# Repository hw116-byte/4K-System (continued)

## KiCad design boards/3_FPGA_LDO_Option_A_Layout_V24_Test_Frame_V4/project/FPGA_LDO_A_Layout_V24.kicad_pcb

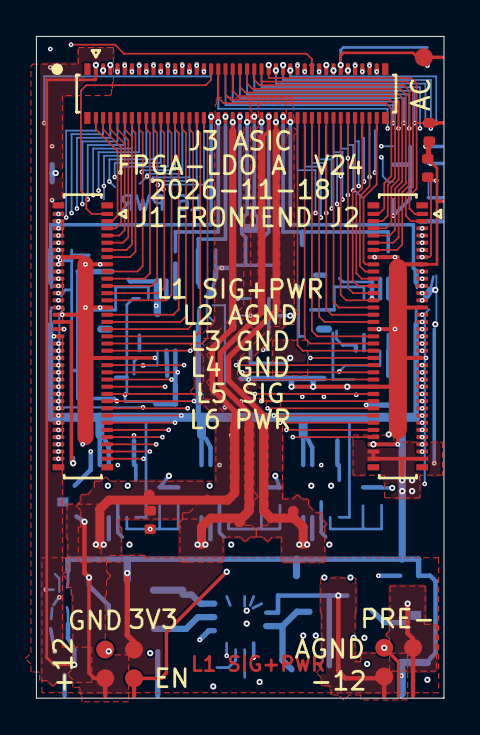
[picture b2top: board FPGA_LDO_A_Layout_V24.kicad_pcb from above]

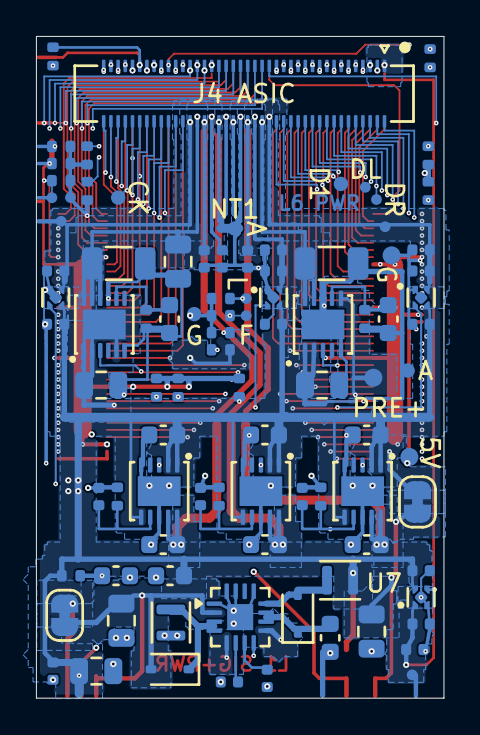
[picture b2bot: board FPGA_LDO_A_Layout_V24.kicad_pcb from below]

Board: 6 copper layers, 22.6 x 36.8 mm, 113 parts (96 on the bottom side), 150 nets.

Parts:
C1, C14, C21: 22uF; C_0805_2012Metric
C2: 100nF; C_0402_1005Metric
C3, C11: 4.7uF; C_0603_1608Metric
C15, C903, C1003: 1uF; C_0603_1608Metric
C16, C17: 10nF; C_0402_1005Metric
C51, C53, C54, C55, C56, C57, C203, C301, C302, C401, C402, C501, C502, C603, C701, C702, C803: 1uF; C_0402_1005Metric
C201, C202, C601, C602, C801, C802: 10uF; C_0603_1608Metric
C901, C1001, C1004: 10uF; C_0805_2012Metric
C902, C1002: 22uF; C_1206_3216Metric
D11, D12: B0540WS-TP; D_SOD-323
J1, J2: DF40C-70DP-0.4V(51); Hirose_DF40C-70DP-0.4V_2x35-1MP_P0.4mm
J3: DF40C-80DP-0.4V(51); Hirose_DF40C-80DP-0.4V_2x40-1MP_P0.4mm
J4: DF40C-80DS-0.4V(51); Hirose_DF40C-80DS-0.4V_2x40_P0.4mm
JP1, JP2: Bridged; SolderJumper-2_P1.3mm_Bridged_RoundedPad1.0x1.5mm
L11, L12: 6.8uH; L_Murata_DFE201610P
NT1: NetTie_2; NetTie-2_SMD_Pad0.5mm
R1, R2, R3, R4, R5, R6, R16, R17, R18, R19, R20, R21, R22, R23, R24, R25, R26, R27, R28: 10k; R_0402_1005Metric
R201, R601: 15k; R_0402_1005Metric
R801: 7.5k; R_0402_1005Metric
R802: 47k; R_0402_1005Metric
R901, R1001: 80.6k; R_0402_1005Metric
TP1: VIN_3V3; TestPoint_Pad_D1.0mm_Compact
TP2: STIM_POS_12V; TestPoint_Pad_D1.0mm_Compact
TP3: STIM_NEG_12V; TestPoint_Pad_D1.0mm_Compact
TP4: EN_ASIC_RAILS; TestPoint_Pad_D1.0mm_Compact
TP5: GND; TestPoint_Pad_D1.0mm_Compact
TP6: AGND; TestPoint_Pad_D1.0mm_Compact
TP7: ASIC_AC_IN; TestPoint_Pad_D1.0mm_Compact
TP8: STIM_PRE_POS; TestPoint_Pad_D1.0mm_Compact
TP9: STIM_PRE_NEG; TestPoint_Pad_D1.0mm_Compact
TP10: VIN_5V; TestPoint_Pad_D1.0mm_Compact
TP11: ASIC_VDD_FE; TestPoint_Pad_D0.6mm_Compact
TP12: ASIC_VDD_ADC; TestPoint_Pad_D0.6mm_Compact
TP14: ASIC_DVDD; TestPoint_Pad_D0.6mm_Compact
TP15: ASIC_REF_VDD; TestPoint_Pad_D0.6mm_Compact
TP16: ASIC_VDD_CGEN; TestPoint_Pad_D0.6mm_Compact
TP17: ASIC_REF_VCM; TestPoint_Pad_D0.6mm_Compact
TP20: ASIC4_SPI_DR; TestPoint_Pad_D0.6mm_Compact
TP21: ASIC4_SPI_DL; TestPoint_Pad_D0.6mm_Compact
TP22: ASIC4_DATA1; TestPoint_Pad_D0.8mm_Compact015
TP23: GND; TestPoint_Pad_D1.0mm_Compact015
TP24: ASIC3_4_TOP_SPI_CLK; TestPoint_Pad_D0.8mm_Compact015
TP25: STIM_START_SHARED; TestPoint_Pad_D0.6mm_Compact
TP26: GND; TestPoint_Pad_D0.6mm_Compact
TP27: BOARD1_SPI_LATCH; TestPoint_Pad_D0.6mm_Compact
TP28: FE_RESET_SHARED; TestPoint_Pad_D0.6mm_Compact
TP29: GND; TestPoint_Pad_D0.8mm_Compact015
TP30, TP31: AGND; TestPoint_Pad_D0.8mm_Compact015
U1: LT3582EUD-12#PBF; QFN-16-1EP_3x3mm_P0.5mm_EP1.45x1.45mm
U2, U6, U8, U9: LT3042EDD#PBF; DFN-10-1EP_3x3mm_P0.5mm_EP1.65x2.38mm
U3, U4, U5, U7: TPS7A2015PDQNR; Texas_X2SON-4_1x1mm_P0.65mm
U10: LT3094EDD#PBF; DFN-12-1EP_3x3mm_P0.45mm_EP1.65x2.38mm

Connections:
/ASIC1_CLK32MHz_Out: J2.59, J4.45
/ASIC1_DATA1: J2.21, J4.79
/ASIC1_DATA2: J2.64, J4.77
/ASIC1_DATA3: J2.62, J4.75
/ASIC1_DATA4: J2.60, J4.73
/ASIC1_DATA5: J2.57, J4.43
/ASIC1_DATA6: J2.55, J4.41
/ASIC1_DATA7: J2.53, J4.39
/ASIC1_DATA8: J2.51, J4.37
/ASIC1_READ: J2.49, J4.35
/ASIC1_SYNC: J2.61, J4.47
/ASIC2_CLK32MHz_Out: J1.63, J4.19
/ASIC2_DATA1: J1.70, J4.33
/ASIC2_DATA2: J1.51, J4.31
/ASIC2_DATA3: J1.53, J4.29
/ASIC2_DATA4: J1.55, J4.27
/ASIC2_DATA5: J1.65, J4.17
/ASIC2_DATA6: J1.67, J4.15
/ASIC2_DATA7: J1.69, J4.13
/ASIC2_DATA8: J1.38, J4.11
/ASIC2_READ: J1.40, J4.9
/ASIC2_SYNC: J1.61, J4.21
/ASIC3_4_TOP_SPI_CLK: J2.37, J4.72, R24.1, TP24.1
/ASIC3_4_TOP_SPI_LATCH: J2.35, J4.70, R26.1
/ASIC3_CLK32MHz_Out: J2.25, J4.62
/ASIC3_DATA1: J2.47, J4.80
/ASIC3_DATA2: J2.45, J4.78
/ASIC3_DATA3: J2.43, J4.76
/ASIC3_DATA4: J2.39, J4.74
/ASIC3_DATA5: J2.23, J4.60
/ASIC3_DATA6: J2.42, J4.58
/ASIC3_DATA7: J1.39, J4.32
/ASIC3_DATA8: J1.43, J4.30
/ASIC3_READ: J1.45, J4.28
/ASIC3_SPI_DL: J2.33, J4.68
/ASIC3_SPI_DR: J2.31, J4.66
/ASIC3_SYNC: J2.29, J4.64
/ASIC4_CLK32MHz_Out: J1.56, J4.12
/ASIC4_DATA1: J1.47, J4.26, TP22.1
/ASIC4_DATA2: J1.49, J4.24
/ASIC4_DATA3: J1.44, J4.22
/ASIC4_DATA4: J1.46, J4.20
/ASIC4_DATA5: J1.58, J4.10
/ASIC4_DATA6: J1.60, J4.8
/ASIC4_DATA7: J1.62, J4.6
/ASIC4_DATA8: J1.64, J4.4
/ASIC4_READ: J1.68, J4.2
/ASIC4_SPI_DL: J1.48, J4.18, TP21.1
/ASIC4_SPI_DR: J1.52, J4.16, TP20.1
/ASIC4_SYNC: J1.54, J4.14
/ASIC5_CLK32MHz_Out: J2.12, J3.45
/ASIC5_DATA1: J2.5, J3.79
/ASIC5_DATA2: J2.7, J3.77
/ASIC5_DATA3: J2.9, J3.75
/ASIC5_DATA4: J2.11, J3.73
/ASIC5_DATA5: J2.10, J3.43
/ASIC5_DATA6: J2.8, J3.41
/ASIC5_DATA7: J2.6, J3.39
/ASIC5_DATA8: J2.4, J3.37
/ASIC5_READ: J2.2, J3.35
/ASIC5_SYNC: J2.3, J3.47
/ASIC6_CLK32MHz_Out: J1.16, J3.19
/ASIC6_DATA1: J1.1, J3.33
/ASIC6_DATA2: J1.28, J3.31
/ASIC6_DATA3: J1.26, J3.29
/ASIC6_DATA4: J1.24, J3.27
/ASIC6_DATA5: J1.12, J3.17
/ASIC6_DATA6: J1.10, J3.15
/ASIC6_DATA7: J1.8, J3.13
/ASIC6_DATA8: J1.6, J3.11
/ASIC6_READ: J1.4, J3.9
/ASIC6_SYNC: J1.18, J3.21
/ASIC7_8_TOP_SPI_CLK: J2.24, J3.72, R25.1
/ASIC7_8_TOP_SPI_LATCH: J2.26, J3.70, R27.1
/ASIC7_CLK32MHz_Out: J2.36, J3.62
/ASIC7_DATA1: J2.16, J3.80
/ASIC7_DATA2: J2.18, J3.78
/ASIC7_DATA3: J2.20, J3.76
/ASIC7_DATA4: J2.22, J3.74
/ASIC7_DATA5: J2.38, J3.60
/ASIC7_DATA6: J2.40, J3.58
/ASIC7_DATA7: J1.37, J3.32
/ASIC7_DATA8: J1.35, J3.30
/ASIC7_READ: J1.33, J3.28
/ASIC7_SPI_DL: J2.28, J3.68
/ASIC7_SPI_DR: J2.30, J3.66
/ASIC7_SYNC: J2.32, J3.64
/ASIC8_CLK32MHz_Out: J1.13, J3.12
/ASIC8_DATA1: J1.31, J3.26
/ASIC8_DATA2: J1.29, J3.24
/ASIC8_DATA3: J1.25, J3.22
/ASIC8_DATA4: J1.23, J3.20
/ASIC8_DATA5: J1.11, J3.10
/ASIC8_DATA6: J1.9, J3.8
/ASIC8_DATA7: J1.7, J3.6
/ASIC8_DATA8: J1.5, J3.4
/ASIC8_READ: J1.3, J3.2
/ASIC8_SPI_DL: J1.21, J3.18
/ASIC8_SPI_DR: J1.19, J3.16
/ASIC8_SYNC: J1.17, J3.14
/ASIC_AC_IN: J3.69, J4.69, R6.1, TP7.1
/ASIC_DVDD: C54.1, C502.1, J3.34, J4.34, R19.2, TP14.1, U5.1
/ASIC_REF_VCM: C57.1, C802.1, J3.40, J4.40, R802.1, TP17.1, U8.9, U8.10
/ASIC_REF_VDD: C55.1, C602.1, J3.52, J4.52, TP15.1, U6.9, U6.10
/ASIC_VDD10: C902.1, J3.36, J4.36, U9.9, U9.10
/ASIC_VDD_ADC: C302.1, J3.56, J4.56, TP12.1, U3.1
/ASIC_VDD_CGEN: C56.1, C702.1, J3.1, J4.1, TP16.1, U7.1
/ASIC_VDD_DRIVER: C53.1, C402.1, J3.38, J4.38, U4.1
/ASIC_VDD_FE: C51.1, C202.1, J3.50, J4.50, TP11.1, U2.9, U2.10
/ASIC_VSS10: C1002.1, C1004.1, J3.54, J4.54, U10.10, U10.11, U10.12
/BOARD1_CLK: J1.42, J4.7, R20.1
/BOARD1_SPI_CLK: J2.52, J4.63, R22.1
/BOARD1_SPI_LATCH: J2.48, J4.61, R18.1, TP27.1
/BOARD3_CLK: J1.2, J3.7, R21.1
/BOARD3_SPI_CLK: J2.13, J3.63, R23.1
/BOARD3_SPI_LATCH: J1.36, J3.61, R28.1
/CAPP: C15.1, D11.1, U1.10, U1.11
/CHIP_RESET_SHARED: J2.58, J3.71, J4.71, R19.1
/EN_ASIC_RAILS: C3.1, R1.2, TP4.1, U1.8, U2.3, U3.3, U4.3, U5.3, U6.3, U7.3, U8.3, U9.3, U10.3
/FE_RESET_SHARED: J2.54, J3.65, J4.65, R16.1, TP28.1
/IMP_TST_SHARED: J2.56, J3.67, J4.67, R17.1
/RAMPN: C17.1, U1.6
/RAMPP: C16.1, U1.7
/STIM_CHB_SHARED: J2.1, J3.49, J4.49, R4.1
/STIM_CHIP1_SPI_DL: J2.46, J4.59
/STIM_CHIP1_SPI_DR: J2.44, J4.57
/STIM_CHIP2_SPI_DL: J1.57, J4.25
/STIM_CHIP2_SPI_DR: J1.59, J4.23
/STIM_CHIP3_SPI_DL: J2.17, J3.59
/STIM_CHIP3_SPI_DR: J2.19, J3.57
/STIM_CHIP4_SPI_DL: J1.22, J3.25
/STIM_CHIP4_SPI_DR: J1.20, J3.23
/STIM_CLK_SHARED: J2.65, J3.53, J4.53, R5.1
/STIM_EN_SHARED: J2.63, J3.51, J4.51, R2.1
/STIM_NEG_12V: C21.1, D12.2, JP2.1, TP3.1, U1.2
/STIM_POS_12V: C14.1, JP1.1, TP2.1, U1.9
/STIM_PRE_NEG: C1001.1, JP2.2, TP9.1, U10.1, U10.2, U10.5, U10.13
/STIM_PRE_POS: C901.1, JP1.2, TP8.1, U9.1, U9.2, U9.6
/STIM_START_SHARED: J2.67, J3.55, J4.55, R3.1, TP25.1
/SW_N: D12.1, L12.1, U1.3, U1.4
/SW_P: D11.2, L11.2, U1.12
/VIN_3V3: C1.1, C2.1, C11.1, C201.1, C301.1, C401.1, C501.1, C601.1, C701.1, C801.1, J2.68, J2.69, J2.70, L11.1, R1.1, TP1.1, U1.5, U2.1, U2.2, U2.6, U3.4, U4.4, U5.4, U6.1, U6.2, U6.6, U7.4, U8.1, U8.2, U8.6
/VIN_5V: J1.32, TP10.1
AGND: C51.2, C53.2, C55.2, C56.2, C57.2, C201.2, C202.2, C203.2, C301.2, C302.2, C401.2, C402.2, C601.2, C602.2, C603.2, C701.2, C702.2, C801.2, C802.2, C803.2, C901.2, C902.2, C903.2, C1001.2, C1002.2, C1003.2, C1004.2, J3.42, J3.44, J4.42, J4.44, NT1.2, R6.2, R201.2, R601.2, R801.2, R802.2, R901.2, R1001.2, TP6.1, TP30.1, TP31.1, U2.5, U2.8, U2.11, U3.2, U3.5, U4.2, U4.5, U6.5, U6.8, U6.11, U7.2, U7.5, U8.5, U8.8, U8.11, U9.5, U9.8, U9.11, U10.6, U10.9
GND: C1.2, C2.2, C3.2, C11.2, C14.2, C15.2, C16.2, C17.2, C21.2, C54.2, C501.2, C502.2, J1.14, J1.15, J1.27, J1.30, J1.34, J1.41, J1.50, J1.66, J2.14, J2.15, J2.27, J2.34, J2.41, J2.50, J2.66, J3.3, J3.5, J3.46, J3.48, J4.3, J4.5, J4.46, J4.48, L12.2, NT1.1, R2.2, R3.2, R4.2, R5.2, R16.2, R17.2, R18.2, R20.2, R21.2, R22.2, R23.2, R24.2, R25.2, R26.2, R27.2, R28.2, TP5.1, TP23.1, TP26.1, TP29.1, U1.1, U1.13, U1.15, U1.16, U1.17, U5.2, U5.5
unnamed: C203.1, R201.1, U2.7
unnamed: C603.1, R601.1, U6.7
unnamed: C803.1, R801.1, U8.7
unnamed: C903.1, R901.1, U9.7
unnamed: C1003.1, R1001.1, U10.8

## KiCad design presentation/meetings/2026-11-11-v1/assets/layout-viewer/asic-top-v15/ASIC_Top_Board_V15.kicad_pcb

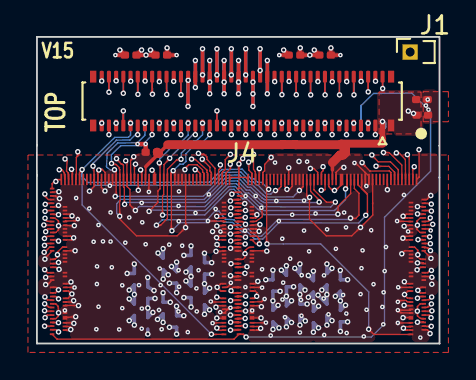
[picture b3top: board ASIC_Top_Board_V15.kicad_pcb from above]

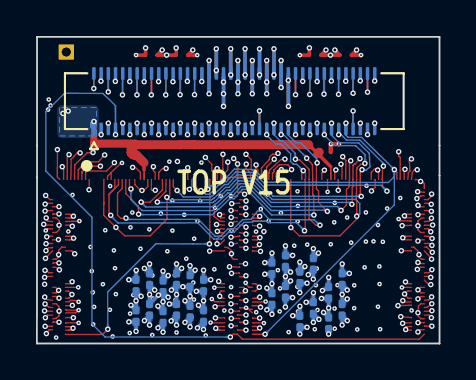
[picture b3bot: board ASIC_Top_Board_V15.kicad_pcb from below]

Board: 10 copper layers, 22.4 x 17.0 mm, 36 parts (25 on the bottom side), 76 nets.

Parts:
C1, C2, C4, C5, C6, C7, C14, C18, C25, C33, C34, C41, C42, C46, C48: 10nF; C_0201_0603Metric
C19, C26, C50, C51, C52, C53, C54, C55, C56, C57, C58, C59, C60, C61, C62, C63: 100nF; C_0201_0603Metric
J1: Conn_01x01_Pin; PinHeader_1x01_P1.00mm_Horizontal
J3: DF40C-80DS-0.4V(51); Hirose_DF40C-80DS-0.4V_2x40_P0.4mm
J4: DF40C-80DP-0.4V(51); Hirose_DF40C-80DP-0.4V_2x40-1MP_P0.4mm
U01_BCD1, U01_BCD2: *; U01_BCD_OFF_CHIP

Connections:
/AC_IN: J3.69, J4.69, U01_BCD1.AC_IN, U01_BCD2.AC_IN
/AGND: C1.2, C2.2, C4.2, C5.2, C6.2, C18.2, C19.2, C25.2, C26.2, C33.2, C34.2, C41.2, C42.2, C46.2, C48.2, C50.2, C51.2, C52.2, C53.2, C54.2, C55.2, C56.2, C57.2, C58.2, C59.2, C60.2, C63.2, J1.1 (Pin_1_1), J3.42, J3.44, J4.42, J4.44, U01_BCD1.AGND2, U01_BCD1.AGND_1, U01_BCD1.LAGND_1, U01_BCD1.LAGND_2, U01_BCD1.LAGND_3, U01_BCD1.LAGND_4, U01_BCD1.LAGND_5, U01_BCD1.LAGND_6, U01_BCD1.LAGND_7, U01_BCD1.LAGND_8, U01_BCD1.LAGND_9, U01_BCD1.LAGND_10, U01_BCD1.LAGND_11, U01_BCD1.LAGND_12, U01_BCD1.LAGND_13, U01_BCD1.LAGND_14, U01_BCD1.LAGND_15, U01_BCD1.LREF_GND1, U01_BCD1.LREF_GND2, U01_BCD1.LREF_GND3, U01_BCD1.LREF_GND4, U01_BCD1.RAGND_1, U01_BCD1.RAGND_2, U01_BCD1.RAGND_3, U01_BCD1.RAGND_4, U01_BCD1.RAGND_5, U01_BCD1.RAGND_6, U01_BCD1.RAGND_7, U01_BCD1.RAGND_8, U01_BCD1.RAGND_9, U01_BCD1.RAGND_10, U01_BCD1.RAGND_11, U01_BCD1.RAGND_12, U01_BCD1.RAGND_13, U01_BCD1.RAGND_14, U01_BCD1.RAGND_15, U01_BCD1.REF_1, U01_BCD1.REF_2, U01_BCD1.REF_3, U01_BCD1.REF_4, U01_BCD1.RREF_GND1, U01_BCD1.RREF_GND2, U01_BCD1.RREF_GND3, U01_BCD1.RREF_GND4, U01_BCD2.AGND2, U01_BCD2.AGND_1, U01_BCD2.LAGND_1, U01_BCD2.LAGND_2, U01_BCD2.LAGND_3, U01_BCD2.LAGND_4, U01_BCD2.LAGND_5, U01_BCD2.LAGND_6, U01_BCD2.LAGND_7, U01_BCD2.LAGND_8, U01_BCD2.LAGND_9, U01_BCD2.LAGND_10, U01_BCD2.LAGND_11, U01_BCD2.LAGND_12, U01_BCD2.LAGND_13, U01_BCD2.LAGND_14, U01_BCD2.LAGND_15, U01_BCD2.LREF_GND1, U01_BCD2.LREF_GND2, U01_BCD2.LREF_GND3, U01_BCD2.LREF_GND4, U01_BCD2.RAGND_1, U01_BCD2.RAGND_2, U01_BCD2.RAGND_3, U01_BCD2.RAGND_4, U01_BCD2.RAGND_5, U01_BCD2.RAGND_6, U01_BCD2.RAGND_7, U01_BCD2.RAGND_8, U01_BCD2.RAGND_9, U01_BCD2.RAGND_10, U01_BCD2.RAGND_11, U01_BCD2.RAGND_12, U01_BCD2.RAGND_13, U01_BCD2.RAGND_14, U01_BCD2.RAGND_15, U01_BCD2.REF_1, U01_BCD2.REF_2, U01_BCD2.REF_3, U01_BCD2.REF_4, U01_BCD2.RREF_GND1, U01_BCD2.RREF_GND2, U01_BCD2.RREF_GND3, U01_BCD2.RREF_GND4
/CHIP_RESET: J3.71, J4.71, U01_BCD1.RRST_DIGITAL, U01_BCD1.RST_DRIVER, U01_BCD2.RRST_DIGITAL, U01_BCD2.RST_DRIVER
/CLK32MHZ: J3.45, J4.45
/CLK32MHZ(2): J3.19, J4.19
/CLKH: J3.7, J4.7, U01_BCD1.CLKH, U01_BCD2.CLKH
/D<1>: J3.79, J4.79
/D<1>(2): J3.33, J4.33
/D<2>: J3.77, J4.77
/D<2>(2): J3.31, J4.31
/D<3>: J3.75, J4.75
/D<3>(2): J3.29, J4.29
/D<4>: J3.73, J4.73
/D<4>(2): J3.27, J4.27
/D<5>: J3.43, J4.43
/D<5>(2): J3.17, J4.17
/D<6>: J3.41, J4.41
/D<6>(2): J3.15, J4.15
/D<7>: J3.39, J4.39
/D<7>(2): J3.13, J4.13
/D<8>: J3.37, J4.37
/D<8>(2): J3.11, J4.11
/DGND: C7.2, C14.2, C61.2, C62.2, J3.3, J3.5, J3.46, J3.48, J4.3, J4.5, J4.46, J4.48, U01_BCD1.DGND1, U01_BCD1.DGND2, U01_BCD1.DGND3, U01_BCD1.DGND4, U01_BCD1.EN_LDO, U01_BCD1.LDGND_1, U01_BCD1.LDGND_2, U01_BCD1.LDGND_3, U01_BCD1.LDGND_4, U01_BCD1.LDGND_5, U01_BCD1.LDGND_6, U01_BCD1.LDGND_7, U01_BCD1.LDGND_8, U01_BCD1.LDGND_9, U01_BCD1.LDGND_10, U01_BCD1.LDGND_11, U01_BCD1.LDGND_12, U01_BCD1.LDGND_13, U01_BCD1.RDGND_1, U01_BCD1.RDGND_2, U01_BCD1.RDGND_3, U01_BCD1.RDGND_4, U01_BCD1.RDGND_5, U01_BCD1.RDGND_6, U01_BCD1.RDGND_7, U01_BCD1.RDGND_8, U01_BCD1.RDGND_9, U01_BCD1.RDGND_10, U01_BCD1.RDGND_11, U01_BCD1.RDGND_12, U01_BCD1.RDGND_13, U01_BCD2.DGND1, U01_BCD2.DGND2, U01_BCD2.DGND3, U01_BCD2.DGND4, U01_BCD2.EN_LDO, U01_BCD2.LDGND_1, U01_BCD2.LDGND_2, U01_BCD2.LDGND_3, U01_BCD2.LDGND_4, U01_BCD2.LDGND_5, U01_BCD2.LDGND_6, U01_BCD2.LDGND_7, U01_BCD2.LDGND_8, U01_BCD2.LDGND_9, U01_BCD2.LDGND_10, U01_BCD2.LDGND_11, U01_BCD2.LDGND_12, U01_BCD2.LDGND_13, U01_BCD2.RDGND_1, U01_BCD2.RDGND_2, U01_BCD2.RDGND_3, U01_BCD2.RDGND_4, U01_BCD2.RDGND_5, U01_BCD2.RDGND_6, U01_BCD2.RDGND_7, U01_BCD2.RDGND_8, U01_BCD2.RDGND_9, U01_BCD2.RDGND_10, U01_BCD2.RDGND_11, U01_BCD2.RDGND_12, U01_BCD2.RDGND_13
/DVDD: C7.1, C14.1, C61.1, C62.1, J3.34, J4.34, U01_BCD1.CGEN_RST, U01_BCD1.LDVDD_B1, U01_BCD1.LDVDD_B2, U01_BCD1.LDVDD_B3, U01_BCD1.LDVDD_T1, U01_BCD1.LDVDD_T2, U01_BCD1.LDVDD_T3, U01_BCD1.RDVDD_B1, U01_BCD1.RDVDD_B2, U01_BCD1.RDVDD_B3, U01_BCD1.RDVDD_T1, U01_BCD1.RDVDD_T2, U01_BCD1.RDVDD_T3, U01_BCD1.SPI_LDO_O, U01_BCD1.SPI_LDO_P, U01_BCD1.SPI_LDO_P1, U01_BCD1.SPI_LDO_P2, U01_BCD2.CGEN_RST, U01_BCD2.LDVDD_B1, U01_BCD2.LDVDD_B2, U01_BCD2.LDVDD_B3, U01_BCD2.LDVDD_T1, U01_BCD2.LDVDD_T2, U01_BCD2.LDVDD_T3, U01_BCD2.RDVDD_B1, U01_BCD2.RDVDD_B2, U01_BCD2.RDVDD_B3, U01_BCD2.RDVDD_T1, U01_BCD2.RDVDD_T2, U01_BCD2.RDVDD_T3, U01_BCD2.SPI_LDO_O, U01_BCD2.SPI_LDO_P, U01_BCD2.SPI_LDO_P1, U01_BCD2.SPI_LDO_P2
/FE_RESET: J3.65, J4.65, U01_BCD1.RST_FEL, U01_BCD1.RST_FER, U01_BCD2.RST_FEL, U01_BCD2.RST_FER
/IMP_TEST: J3.67, J4.67, U01_BCD1.IMP_TST, U01_BCD2.IMP_TST
/READ: J3.35, J4.35
/READ(2): J3.9, J4.9
/REF_VCM: C5.1, C46.1, C57.1, C58.1, J3.40, J4.40, U01_BCD1.LREF_VCM1, U01_BCD1.LREF_VCM2, U01_BCD1.LREF_VCM3, U01_BCD1.LREF_VCM4, U01_BCD1.RREF_VCM1, U01_BCD1.RREF_VCM2, U01_BCD1.RREF_VCM3, U01_BCD1.RREF_VCM4, U01_BCD1.VCM, U01_BCD2.LREF_VCM1, U01_BCD2.LREF_VCM2, U01_BCD2.LREF_VCM3, U01_BCD2.LREF_VCM4, U01_BCD2.RREF_VCM1, U01_BCD2.RREF_VCM2, U01_BCD2.RREF_VCM3, U01_BCD2.RREF_VCM4, U01_BCD2.VCM
/REF_VDD: C2.1, C33.1, C55.1, C56.1, J3.52, J4.52, U01_BCD1.LREF_VDD1, U01_BCD1.LREF_VDD2, U01_BCD1.LREF_VDD3, U01_BCD1.LREF_VDD4, U01_BCD1.RREF_VDD1, U01_BCD1.RREF_VDD2, U01_BCD1.RREF_VDD3, U01_BCD1.RREF_VDD4, U01_BCD2.LREF_VDD1, U01_BCD2.LREF_VDD2, U01_BCD2.LREF_VDD3, U01_BCD2.LREF_VDD4, U01_BCD2.RREF_VDD1, U01_BCD2.RREF_VDD2, U01_BCD2.RREF_VDD3, U01_BCD2.RREF_VDD4
/SPI_CLK: J3.63, J4.63
/SPI_DINL: J3.59, J4.59
/SPI_DINL(2): J3.25, J4.25
/SPI_DINR: J3.57, J4.57
/SPI_DINR(2): J3.23, J4.23
/SPI_LATCH: J3.61, J4.61
/STIM_CHB: J3.49, J4.49, U01_BCD1.FPGA_CHBL, U01_BCD1.FPGA_CHBR, U01_BCD2.FPGA_CHBL, U01_BCD2.FPGA_CHBR
/STIM_CLK: J3.53, J4.53, U01_BCD1.FPGA_CLK, U01_BCD2.FPGA_CLK
/STIM_EN: J3.51, J4.51, U01_BCD1.FPGA_EN, U01_BCD2.FPGA_EN
/STIM_START: J3.55, J4.55, U01_BCD1.FPGA_START, U01_BCD2.FPGA_START
/SYNC: J3.47, J4.47
/SYNC(2): J3.21, J4.21
/T_CLK32MHZ: J3.62, J4.62, U01_BCD1.CLK32MHZ
/T_CLK32MHZ(2): J3.12, J4.12, U01_BCD2.CLK32MHZ
/T_D<1>: J3.80, J4.80, U01_BCD1.DATAL<4>
/T_D<1>(2): J3.26, J4.26, U01_BCD2.DATAL<4>
/T_D<2>: J3.78, J4.78, U01_BCD1.DATAL<3>
/T_D<2>(2): J3.24, J4.24, U01_BCD2.DATAL<3>
/T_D<3>: J3.76, J4.76, U01_BCD1.DATAL<2>
/T_D<3>(2): J3.22, J4.22, U01_BCD2.DATAL<2>
/T_D<4>: J3.74, J4.74, U01_BCD1.DATAL<1>
/T_D<4>(2): J3.20, J4.20, U01_BCD2.DATAL<1>
/T_D<5>: J3.60, J4.60, U01_BCD1.DATAR<4>
/T_D<5>(2): J3.10, J4.10, U01_BCD2.DATAR<4>
/T_D<6>: J3.58, J4.58, U01_BCD1.DATAR<3>
/T_D<6>(2): J3.8, J4.8, U01_BCD2.DATAR<3>
/T_D<7>: J3.32, J4.32, U01_BCD1.DATAR<2>
/T_D<7>(2): J3.6, J4.6, U01_BCD2.DATAR<2>
/T_D<8>: J3.30, J4.30, U01_BCD1.DATAR<1>
/T_D<8>(2): J3.4, J4.4, U01_BCD2.DATAR<1>
/T_READ: J3.28, J4.28, U01_BCD1.READ
/T_READ(2): J3.2, J4.2, U01_BCD2.READ
/T_SPI_CLK: J3.72, J4.72, U01_BCD1.SPI_CLK, U01_BCD2.SPI_CLK
/T_SPI_DINL: J3.68, J4.68, U01_BCD1.SPI_DINL
/T_SPI_DINL(2): J3.18, J4.18, U01_BCD2.SPI_DINL
/T_SPI_DINR: J3.66, J4.66, U01_BCD1.SPI_DINR
/T_SPI_DINR(2): J3.16, J4.16, U01_BCD2.SPI_DINR
/T_SPI_LATCH: J3.70, J4.70, U01_BCD1.SPI_LATCH, U01_BCD2.SPI_LATCH
/T_SYNC: J3.64, J4.64, U01_BCD1.SYNC
/T_SYNC(2): J3.14, J4.14, U01_BCD2.SYNC
/VDD10: C18.1, C19.1, J3.36, J4.36, U01_BCD1.P10_L, U01_BCD1.P10_R, U01_BCD2.P10_L, U01_BCD2.P10_R
/VDD_ADC: C1.1, C34.1, C53.1, C54.1, J3.56, J4.56, U01_BCD1.LVDD_ADC1, U01_BCD1.LVDD_ADC2, U01_BCD1.LVDD_ADC3, U01_BCD1.LVDD_ADC4, U01_BCD1.LVDD_ADC5, U01_BCD1.RVDD_ADC1, U01_BCD1.RVDD_ADC2, U01_BCD1.RVDD_ADC3, U01_BCD1.RVDD_ADC4, U01_BCD1.RVDD_ADC5, U01_BCD2.LVDD_ADC1, U01_BCD2.LVDD_ADC2, U01_BCD2.LVDD_ADC3, U01_BCD2.LVDD_ADC4, U01_BCD2.LVDD_ADC5, U01_BCD2.RVDD_ADC1, U01_BCD2.RVDD_ADC2, U01_BCD2.RVDD_ADC3, U01_BCD2.RVDD_ADC4, U01_BCD2.RVDD_ADC5
/VDD_CGEN: C6.1, C50.1, C63.1, J3.1, J4.1, U01_BCD1.VDD_CGEN, U01_BCD2.VDD_CGEN
/VDD_DRIVER: C41.1, C42.1, C59.1, C60.1, J3.38, J4.38, U01_BCD1.LVDD_DRIVER1, U01_BCD1.LVDD_DRIVER2, U01_BCD1.LVDD_DRIVER3, U01_BCD1.LVDD_DRIVER4, U01_BCD1.LVDD_DRIVER5, U01_BCD1.RVDD_DRIVER1, U01_BCD1.RVDD_DRIVER2, U01_BCD1.RVDD_DRIVER3, U01_BCD1.RVDD_DRIVER4, U01_BCD1.RVDD_DRIVER5, U01_BCD2.LVDD_DRIVER1, U01_BCD2.LVDD_DRIVER2, U01_BCD2.LVDD_DRIVER3, U01_BCD2.LVDD_DRIVER4, U01_BCD2.LVDD_DRIVER5, U01_BCD2.RVDD_DRIVER1, U01_BCD2.RVDD_DRIVER2, U01_BCD2.RVDD_DRIVER3, U01_BCD2.RVDD_DRIVER4, U01_BCD2.RVDD_DRIVER5
/VDD_FE: C4.1, C48.1, C51.1, C52.1, J3.50, J4.50, U01_BCD1.LVDD_FE1, U01_BCD1.LVDD_FE2, U01_BCD1.LVDD_FE3, U01_BCD1.LVDD_FE4, U01_BCD1.RVDD_FE1, U01_BCD1.RVDD_FE2, U01_BCD1.RVDD_FE3, U01_BCD1.RVDD_FE4, U01_BCD2.LVDD_FE1, U01_BCD2.LVDD_FE2, U01_BCD2.LVDD_FE3, U01_BCD2.LVDD_FE4, U01_BCD2.RVDD_FE1, U01_BCD2.RVDD_FE2, U01_BCD2.RVDD_FE3, U01_BCD2.RVDD_FE4
/VSS10: C25.1, C26.1, J3.54, J4.54, U01_BCD1.M10_L, U01_BCD1.M10_R, U01_BCD2.M10_L, U01_BCD2.M10_R

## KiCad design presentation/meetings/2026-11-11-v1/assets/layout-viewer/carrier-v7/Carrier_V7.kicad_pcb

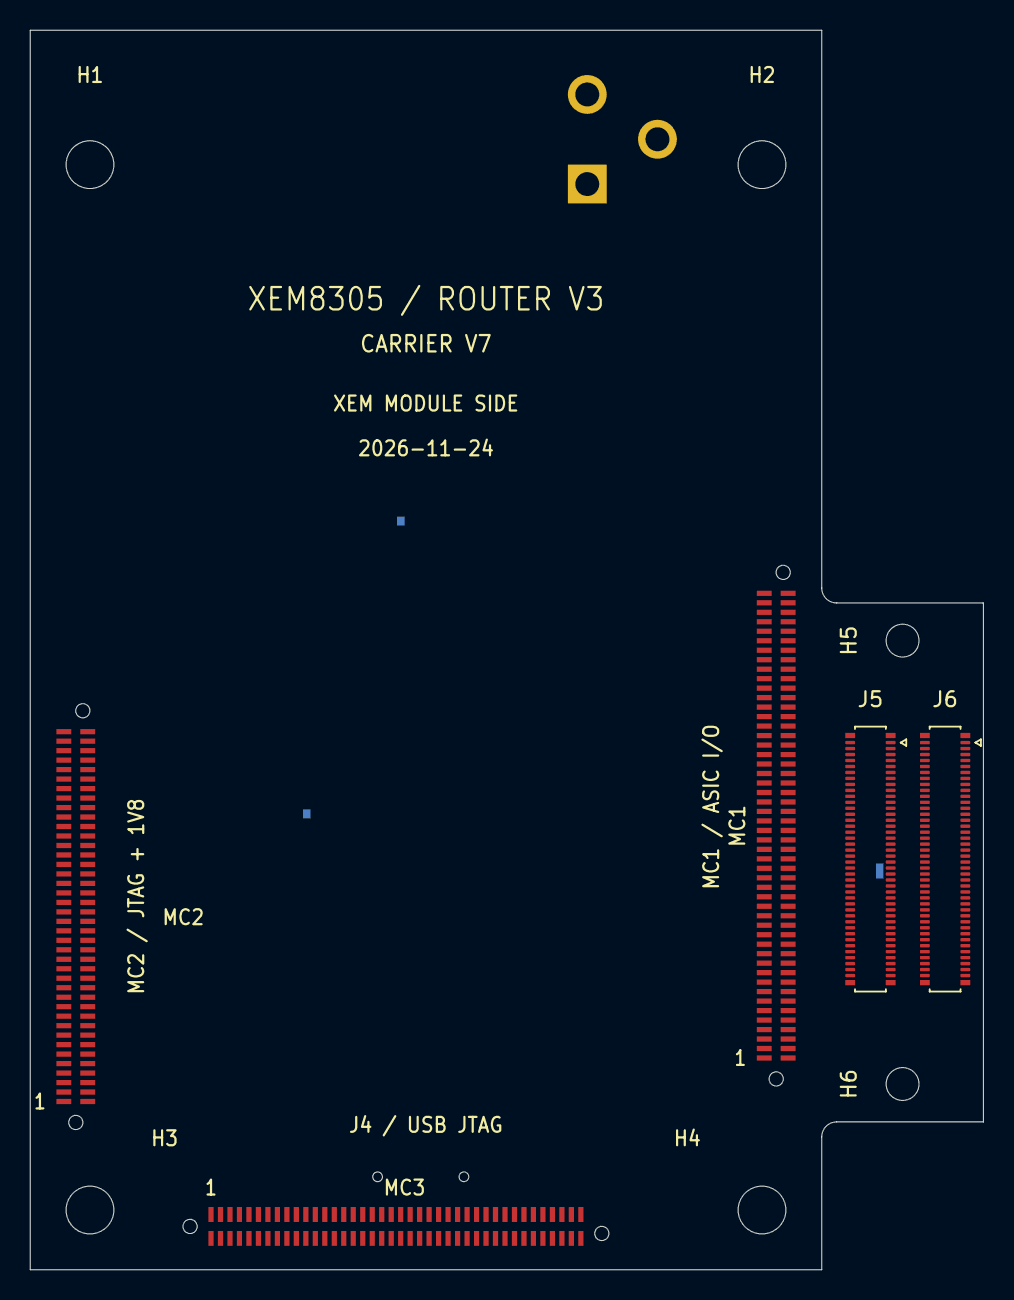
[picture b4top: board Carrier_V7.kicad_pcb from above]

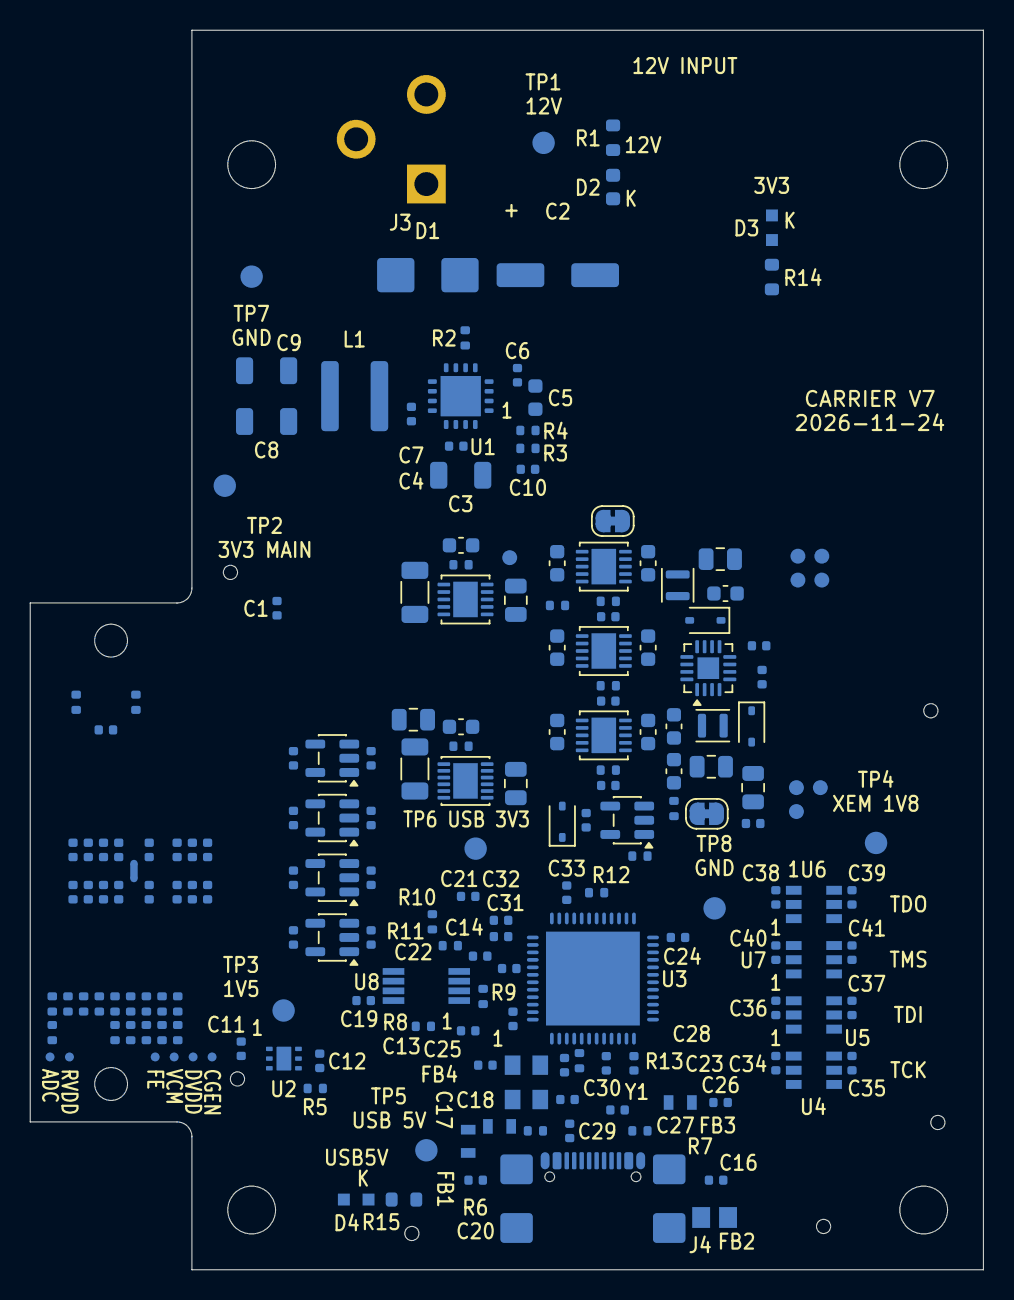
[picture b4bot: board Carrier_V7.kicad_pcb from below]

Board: 6 copper layers, 63.8 x 83.0 mm, 203 parts (192 on the bottom side), 193 nets, no tracks yet.

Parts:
C1: 0.1u 25v; C_0402_1005Metric
C2: 220u 25v; CP_Panasonic_EEEFTE221XAL_D6.3x7.7_V3
C3: 22u 35V; C_1206_3216Metric
C4: 0.1u 25V; C_0402_1005Metric
C5: 1u 25V; C_0603_1608Metric
C6: 3.3n 50V; C_0402_1005Metric
C7: 0.1u 16V; C_0402_1005Metric
C8, C9: 22u 10V; C_1206_3216Metric
C10: 10p 50V; C_0402_1005Metric
C11, C12: 4.7u 10V X5R; C_0402_1005Metric
C13, C21, C26, C27, C29: 4.7u; C_0402_1005Metric
C14, C16, C19, C22, C23, C24, C25, C28, C30, C31, C32, C34, C35, C36, C37, C38, C39, C40, C41: 100n; C_0402_1005Metric
C15, C903, C1003: 1uF; C_0603_1608Metric
C17, C18: 18p; C_0402_1005Metric
C20, C33: 10n; C_0402_1005Metric
C42, C46, C49: 22uF; C_0805_2012Metric
C43, C68: 100nF; C_0402_1005Metric
C44, C45: 4.7uF; C_0603_1608Metric
C47, C48: 10nF; C_0402_1005Metric
C51, C52, C53, C54, C55, C56, C57, C58, C59, C60, C61, C62, C63, C64, C65, C66, C67, C203, C301, C302, C401, C402, C501, C502, C603, C701, C702, C803: 1uF; C_0402_1005Metric
C201, C202, C601, C602, C801, C802: 10uF; C_0603_1608Metric
C901, C1001, C1004: 10uF; C_0805_2012Metric
C902, C1002: 22uF; C_1206_3216Metric
D1: SMBJ15CA-13-F; D_SMB
D2: 598-8070-107F; LED_0603_1608Metric
D3: APT1608LZGCK; LED_Kingbright_APT1608LZGCK_V2
D4: APT1608LSYCK/J3-PRV; LED_Kingbright_APT1608LSYCK_J3_PRV_V2
D11, D12, D13: B0540WS-TP; D_SOD-323
FB1, FB3, FB4: 600R; Ferrite_Bead_Murata_BLM18KG601SN1D_0603_V4
FB2: 220R @100MHz; BRK8305_A03_FB503
H1, H2, H3, H4: XEM M3 NPTH; MountingHole_3.2mm_XEM_M3_Keepout
H5, H6: M2 holder NPTH; MountingHole_2.2mm_M2
J3: PJ-102AH; PJ102AH
J4: USB4110-GF-A; USB_C_Receptacle_GCT_USB4110_GF_A_Horizontal
J5, J6: DF40C-80DP-0.4V(51); Hirose_DF40C-80DP-0.4V_2x40-1MP_P0.4mm
JP1, JP2: Bridged; SolderJumper-2_P1.3mm_Bridged_RoundedPad1.0x1.5mm
L1: 2.2uH; L_Coilcraft_XAL5030-332MEC
L11, L12: 6.8uH; L_Murata_DFE201610P
MC1: ERF6-50-03.5-L-DV-A-K-TR
MC2: XEM_MC2_80; ERF6-40-03.5-L-DV-A-K-TR
MC3: XEM_MC3_80; ERF6-40-03.5-L-DV-A-K-TR
NT1: NetTie_2; NetTie-2_SMD_Pad0.5mm
R1: 2.0k; R_0603_1608Metric
R2: 10k 1%; R_0402_1005Metric
R3: 73.2k 1%; R_0402_1005Metric
R4: 22.1k 1%; R_0402_1005Metric
R5, R8, R9: 100k; R_0402_1005Metric
R6, R7: 5.1k 1%; R_0402_1005Metric
R10: 2k; R_0402_1005Metric
R11, R12, R16, R17, R18, R19, R20, R21, R22, R23, R24, R25, R26, R27, R28, R29, R30, R31, R32, R33: 10k; R_0402_1005Metric
R13: 12k 1%; R_0402_1005Metric
R14: 3.0k 1%; R_0603_1608Metric
R15: 6.8k 1%; R_0603_1608Metric
R34: 220; R_0402_1005Metric
R201, R601: 15k; R_0402_1005Metric
R801: 7.5k; R_0402_1005Metric
R802: 47k; R_0402_1005Metric
R901, R1001: 80.6k; R_0402_1005Metric
TP1: 12V; TestPoint_Pad_D1.5mm
TP2: 3V3_MAIN; TestPoint_Pad_D1.5mm
TP3: 1V5; TestPoint_Pad_D1.5mm
TP4: XEM_1V8; TestPoint_Pad_D1.5mm
TP5: USB_5V; TestPoint_Pad_D1.5mm
TP6: USB_3V3; TestPoint_Pad_D1.5mm
TP7: GND_PWR; TestPoint_Pad_D1.5mm
TP8: GND_USB; TestPoint_Pad_D1.5mm
TP11: ASIC_VDD_FE; TestPoint_Pad_D0.6mm_Compact
TP12: ASIC_VDD_ADC; TestPoint_Pad_D0.6mm_Compact
TP14: ASIC_DVDD; TestPoint_Pad_D0.6mm_Compact
TP15: ASIC_REF_VDD; TestPoint_Pad_D0.6mm_Compact
TP16: ASIC_VDD_CGEN; TestPoint_Pad_D0.6mm_Compact
TP17: ASIC_REF_VCM; TestPoint_Pad_D0.6mm_Compact
TP31: +3V3; TestPoint_Pad_D1.0mm_Compact
TP32: STIM_POS_12V; TestPoint_Pad_D1.0mm_Compact
TP33: STIM_NEG_12V; TestPoint_Pad_D1.0mm_Compact
TP34: EN_ASIC_RAILS; TestPoint_Pad_D1.0mm_Compact
TP35: GND; TestPoint_Pad_D1.0mm_Compact
TP36: AGND; TestPoint_Pad_D1.0mm_Compact
TP38: STIM_PRE_POS; TestPoint_Pad_D1.0mm_Compact
TP39: STIM_PRE_NEG; TestPoint_Pad_D1.0mm_Compact
U1: TPS54429ERSAT; TPS54429E_RSA
U2: TLV75515PDRVR; Texas_WSON-6_2x2mm_P0.65mm_EP1x1.6mm_TLV755_DRV_V2
U3: FT232HQ; BRK8305_A03_U501
U4, U5, U6, U7: SN74AXC1T45DBVR; BRK8305_A03_U500
U8: 93AA56B-I/MS; BRK8305_A03_U505
U11: LT3582EUD-12#PBF; QFN-16-1EP_3x3mm_P0.5mm_EP1.45x1.45mm
U12, U16, U18, U19: LT3042EDD#PBF; DFN-10-1EP_3x3mm_P0.5mm_EP1.65x2.38mm
U13, U14, U15, U17: TPS7A2015PDBVR; SOT-23-5
U20: LT3094EDD#PBF; DFN-12-1EP_3x3mm_P0.45mm_EP1.65x2.38mm
U21: SN74LV1T34DBVR; SOT-23-5
Y1: 12MHz; BRK8305_A03_Y500

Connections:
+1V5: C11.1, MC1.1, MC1.2, MC1.3, MC1.4, MC2.37, MC2.39, MC2.41, MC2.43, TP3.1, U2.1
+3V3: C8.1, C9.1, C10.1, C12.1, C42.1, C43.1, C45.1, C68.1, C201.1, C301.1, C401.1, C501.1, C601.1, C701.1, C801.1, L1.2, L11.1, R3.1, R14.1, TP2.1, TP31.1, U1.16, U2.6, U11.5, U12.1, U12.2, U12.6, U13.1, U14.1, U15.1, U16.1, U16.2, U16.6, U17.1, U18.1, U18.2, U18.6, U21.5
+12V: C1.1, C2.1, C3.1, C4.1, D1.2, J3.1, MC1.91, MC1.93, MC1.95, MC1.97, MC1.99, R1.1, R2.1, TP1.1, U1.13, U1.14, U1.15
/ASIC_Rails/ASIC_EN_SRC: D13.1, R29.1, U21.4
/ASIC_Rails/CAPP: C15.1, D11.1, U11.10, U11.11
/ASIC_Rails/EN_ASIC_RAILS: C44.1, R29.2, R34.2, TP34.1, U11.8, U12.3, U13.3, U14.3, U15.3, U16.3, U17.3, U18.3, U19.3, U20.3
/ASIC_Rails/RAMPN: C48.1, U11.6
/ASIC_Rails/RAMPP: C47.1, U11.7
/ASIC_Rails/STIM_NEG_12V: C49.1, D12.2, JP2.1, TP33.1, U11.2
/ASIC_Rails/STIM_POS_12V: C46.1, JP1.1, TP32.1, U11.9
/ASIC_Rails/STIM_PRE_NEG: C1001.1, JP2.2, TP39.1, U20.1, U20.2, U20.5, U20.13
/ASIC_Rails/STIM_PRE_POS: C901.1, JP1.2, TP38.1, U19.1, U19.2, U19.6
/ASIC_Rails/SW_N: D12.1, L12.1, U11.3, U11.4
/ASIC_Rails/SW_P: D11.2, L11.2, U11.12
/Router_Interface/ASIC_AC_IN: J5.69, J6.70
/XEM_Power_USB/FB_BUCK: C10.2, R3.2, R4.1, U1.1
/XEM_Power_USB/USBJTAG_1.8V_ANALOG: C32.2, U3.37
/XEM_Power_USB/USBJTAG_1.8V_CORE: C31.2, U3.38
/XEM_Power_USB/USBJTAG_3.3V: C19.1, C21.1, C22.1, C23.1, C24.1, C25.1, C26.1, C34.1, C36.1, C38.1, C40.1, FB3.1, FB4.1, R9.1, R11.2, R12.1, TP6.1, U3.12, U3.24, U3.39, U3.46, U4.1, U4.5, U5.1, U5.5, U6.1, U7.1, U7.5, U8.8
/XEM_Power_USB/USBJTAG_3.3V_PHY: C29.1, C30.1, FB4.2, U3.3
/XEM_Power_USB/USBJTAG_3.3V_PLL: C27.1, C28.1, FB3.2, U3.8
/XEM_Power_USB/USBJTAG_5V_FILTERED: C13.1, C14.1, FB1.2, U3.40
/XEM_Power_USB/USBJTAG_EECLK: R9.2, U3.44, U8.2
/XEM_Power_USB/USBJTAG_EECS: R8.1, U3.45, U8.1
/XEM_Power_USB/USBJTAG_EEDATA: R10.1, U3.43, U8.3
/XEM_Power_USB/XEM_1.8V: C35.1, C37.1, C39.1, C41.1, MC2.75, MC2.77, MC2.79, TP4.1, U4.6, U5.6, U6.6, U7.6
AGND: C51.2, C52.2, C53.2, C55.2, C56.2, C57.2, C58.2, C59.2, C61.2, C62.2, C63.2, C64.2, C65.2, C66.2, C67.2, C201.2, C202.2, C203.2, C301.2, C302.2, C401.2, C402.2, C601.2, C602.2, C603.2, C701.2, C702.2, C801.2, C802.2, C803.2, C901.2, C902.2, C903.2, C1001.2, C1002.2, C1003.2, C1004.2, J5.42, J5.44, J6.41, J6.43, NT1.2, R201.2, R601.2, R801.2, R802.2, R901.2, R1001.2, TP36.1, U12.5, U12.8, U12.11, U13.2, U14.2, U16.5, U16.8, U16.11, U17.2, U18.5, U18.8, U18.11, U19.5, U19.8, U19.11, U20.6, U20.9
ASIC1_CLK32MHz_Out: J6.46, MC1.52
ASIC1_DATA1: J6.80, MC1.50
ASIC1_DATA2: J6.78, MC1.54
ASIC1_DATA3: J6.76, MC1.49
ASIC1_DATA4: J6.74, MC1.55
ASIC1_DATA5: J6.44, MC1.48
ASIC1_DATA6: J6.42, MC1.47
ASIC1_DATA7: J6.40, MC1.57
ASIC1_DATA8: J6.38, MC1.46
ASIC1_READ: J6.36, MC1.53
ASIC1_SYNC: J6.48, MC1.51
ASIC2_CLK32MHz_Out: J6.20, MC1.56
ASIC2_DATA1: J6.34, MC1.60
ASIC2_DATA2: J6.32, MC1.64
ASIC2_DATA3: J6.30, MC1.65
ASIC2_DATA4: J6.28, MC1.66
ASIC2_DATA5: J6.18, MC1.45
ASIC2_DATA6: J6.16, MC1.44
ASIC2_DATA7: J6.14, MC1.68
ASIC2_DATA8: J6.12, MC1.43
ASIC2_READ: J6.10, MC1.59
ASIC2_SYNC: J6.22, MC1.58
ASIC3_4_TOP_SPI_CLK: J6.71, MC2.55, R24.1
ASIC3_4_TOP_SPI_LATCH: J6.69, MC2.54, R26.1
ASIC3_CLK32MHz_Out: J6.61, MC1.63
ASIC3_DATA1: J6.79, MC1.71
ASIC3_DATA2: J6.77, MC1.72
ASIC3_DATA3: J6.75, MC1.73
ASIC3_DATA4: J6.73, MC1.74
ASIC3_DATA5: J6.59, MC1.75
ASIC3_DATA6: J6.57, MC1.76
ASIC3_DATA7: J6.31, MC1.77
ASIC3_DATA8: J6.29, MC1.78
ASIC3_READ: J6.27, MC1.70
ASIC3_SPI_DL: J6.67, MC2.52
ASIC3_SPI_DR: J6.65, MC2.51
ASIC3_SYNC: J6.63, MC1.69
ASIC4_CLK32MHz_Out: J6.11, MC1.67
ASIC4_DATA1: J6.25, MC1.81
ASIC4_DATA2: J6.23, MC1.82
ASIC4_DATA3: J6.21, MC1.83
ASIC4_DATA4: J6.19, MC1.84
ASIC4_DATA5: J6.9, MC1.85
ASIC4_DATA6: J6.7, MC1.86
ASIC4_DATA7: J6.5, MC1.88
ASIC4_DATA8: J6.3, MC1.42
ASIC4_READ: J6.1, MC1.80
ASIC4_SPI_DL: J6.17, MC1.37
ASIC4_SPI_DR: J6.15, MC1.36
ASIC4_SYNC: J6.13, MC1.79
ASIC5_CLK32MHz_Out: J5.45, MC1.9
ASIC5_DATA1: J5.79, MC1.12
ASIC5_DATA2: J5.77, MC1.14
ASIC5_DATA3: J5.75, MC1.15
ASIC5_DATA4: J5.73, MC1.16
ASIC5_DATA5: J5.43, MC1.17
ASIC5_DATA6: J5.41, MC1.18
ASIC5_DATA7: J5.39, MC1.19
ASIC5_DATA8: J5.37, MC1.20
ASIC5_READ: J5.35, MC1.11
ASIC5_SYNC: J5.47, MC1.10
ASIC6_CLK32MHz_Out: J5.19, MC1.13
ASIC6_DATA1: J5.33, MC1.23
ASIC6_DATA2: J5.31, MC1.24
ASIC6_DATA3: J5.29, MC1.25
ASIC6_DATA4: J5.27, MC1.27
ASIC6_DATA5: J5.17, MC1.28
ASIC6_DATA6: J5.15, MC1.29
ASIC6_DATA7: J5.13, MC1.31
ASIC6_DATA8: J5.11, MC1.32
ASIC6_READ: J5.9, MC1.22
ASIC6_SYNC: J5.21, MC1.21
ASIC7_8_TOP_SPI_CLK: J5.72, MC2.65, R25.1
ASIC7_8_TOP_SPI_LATCH: J5.70, MC2.63, R27.1
ASIC7_CLK32MHz_Out: J5.62, MC2.22
ASIC7_DATA1: J5.80, MC2.24
ASIC7_DATA2: J5.78, MC2.19
ASIC7_DATA3: J5.76, MC2.25
ASIC7_DATA4: J5.74, MC2.17
ASIC7_DATA5: J5.60, MC2.28
ASIC7_DATA6: J5.58, MC2.15
ASIC7_DATA7: J5.32, MC2.29
ASIC7_DATA8: J5.30, MC2.30
ASIC7_READ: J5.28, MC2.23
ASIC7_SPI_DL: J5.68, MC2.62
ASIC7_SPI_DR: J5.66, MC2.61
ASIC7_SYNC: J5.64, MC2.21
ASIC8_CLK32MHz_Out: J5.12, MC2.26
ASIC8_DATA1: J5.26, MC2.34
ASIC8_DATA2: J5.24, MC2.36
ASIC8_DATA3: J5.22, MC2.38
ASIC8_DATA4: J5.20, MC2.13
ASIC8_DATA5: J5.10, MC2.40
ASIC8_DATA6: J5.8, MC2.11
ASIC8_DATA7: J5.6, MC2.42
ASIC8_DATA8: J5.4, MC2.44
ASIC8_READ: J5.2, MC2.33
ASIC8_SPI_DL: J5.18, MC2.27
ASIC8_SPI_DR: J5.16, MC1.30
ASIC8_SYNC: J5.14, MC2.32
ASIC_DVDD: C54.1, C60.1, C502.1, J5.34, J6.33, R19.2, TP14.1, U15.5
ASIC_REF_VCM: C57.1, C63.1, C802.1, J5.40, J6.39, R802.1, TP17.1, U18.9, U18.10
ASIC_REF_VDD: C55.1, C65.1, C602.1, J5.52, J6.51, TP15.1, U16.9, U16.10
ASIC_VDD10: C52.1, C61.1, C902.1, J5.36, J6.35, U19.9, U19.10
ASIC_VDD_ADC: C59.1, C67.1, C302.1, J5.56, J6.55, TP12.1, U13.5
ASIC_VDD_CGEN: C56.1, C702.1, J5.1, J6.2, TP16.1, U17.5
ASIC_VDD_DRIVER: C53.1, C62.1, C402.1, J5.38, J6.37, U14.5
ASIC_VDD_FE: C51.1, C64.1, C202.1, J5.50, J6.49, TP11.1, U12.9, U12.10
ASIC_VSS10: C58.1, C66.1, C1002.1, C1004.1, J5.54, J6.53, U20.10, U20.11, U20.12
BOARD1_CLK: J6.8, MC1.35, R20.1
BOARD1_SPI_CLK: J6.64, MC2.50, R22.1
BOARD1_SPI_LATCH: J6.62, MC2.48, R18.1
BOARD3_CLK: J5.7, MC1.26, R21.1
BOARD3_SPI_CLK: J5.63, MC2.60, R23.1
BOARD3_SPI_LATCH: J5.61, MC2.59, R28.1
CHIP_RESET_SHARED: J5.71, J6.72, MC2.53, R19.1
FE_RESET_SHARED: J5.65, J6.66, MC2.71, R16.1
GND: C1.2, C2.2, C3.2, C4.2, C5.1, C6.1, C8.2, C9.2, C11.2, C12.2, C13.2, C14.2, C15.2, C16.2, C17.2, C18.2, C19.2, C20.1, C21.2, C22.2, C23.2, C24.2, C25.2, C26.2, C27.2, C28.2, C29.2, C30.2, C31.1, C32.1, C33.2, C34.2, C35.2, C36.2, C37.2, C38.2, C39.2, C40.2, C41.2, C42.2, C43.2, C44.2, C45.2, C46.2, C47.2, C48.2, C49.2, C54.2, C60.2, C68.2, C501.2, C502.2, D1.1, D2.1, D3.1, D4.1, FB2.1, J3.2, J4.A1, J4.A12, J4.B1, J4.B12, J5.3, J5.5, J5.46, J5.48, J6.4, J6.6, J6.45, J6.47, L12.2, MC1.5, MC1.6, MC1.7, MC1.8, MC1.33, MC1.34, MC1.61, MC1.62, MC1.92, MC1.94, MC1.96, MC1.98, MC1.100, MC2.6, MC2.9, MC2.20, MC2.35, MC2.45, MC2.46, MC2.47, MC2.72, MC2.73, MC2.74, MC2.76, MC3.1, MC3.2, MC3.7, MC3.8, MC3.13, MC3.14, MC3.19, MC3.20, MC3.25, MC3.26, MC3.31, MC3.32, MC3.37, MC3.38, MC3.43, MC3.44, MC3.49, MC3.50, MC3.55, MC3.56, MC3.61, MC3.62, MC3.67, MC3.68, MC3.73, MC3.74, MC3.79, MC3.80, NT1.1, R4.2, R5.2, R6.1, R7.2, R8.2, R13.2, R16.2, R17.2, R18.2, R20.2, R21.2, R22.2, R23.2, R24.2, R25.2, R26.2, R27.2, R28.2, R30.2, R31.2, R32.2, R33.2, TP7.1, TP8.1, TP35.1, U1.4, U1.7, U1.8, U1.17, U2.3, U2.7, U3.4, U3.9, U3.10, U3.11, U3.22, U3.23, U3.35, U3.36, U3.41, U3.42, U3.47, U3.48, U3.PAD, U4.2, U5.2, U6.2, U6.5, U7.2, U8.5, U11.1, U11.13, U11.15, U11.16, U11.17, U15.2, U21.3, Y1.2, Y1.4
IMP_TST_SHARED: J5.67, J6.68, MC2.49, R17.1
JTAG_TCK_1.8V: MC2.1, U4.4
JTAG_TDI_1.8V: MC2.3, U5.4
JTAG_TDO_1.8V: MC2.7, U6.4
JTAG_TMS_1.8V: MC2.5, U7.4
unnamed: C16.1, FB2.2, J4.M1, J4.M2, J4.M3, J4.M4
unnamed: D2.2, R1.2
unnamed: D3.2, R14.2
unnamed: D4.2, R15.2
unnamed: D13.2, R34.1
unnamed: J4.A5, R6.2
unnamed: J4.B5, R7.1
unnamed: MC2.14, MC2.16
unnamed: R2.2, U1.6
unnamed: C6.2, U1.3
unnamed: C7.2, L1.1, U1.9, U1.10, U1.11
unnamed: C7.1, U1.12
unnamed: C5.2, U1.2
unnamed: U3.13, U4.3
unnamed: U3.14, U5.3
unnamed: U3.15, U6.3
unnamed: U3.16, U7.3
unnamed: C17.1, U3.1, Y1.1
unnamed: C18.1, U3.2, Y1.3
unnamed: R13.1, U3.5
unnamed: C33.1, R12.2, U3.34
unnamed: R10.2, R11.1, U8.4
unnamed: C203.1, R201.1, U12.7
unnamed: C603.1, R601.1, U16.7
unnamed: C803.1, R801.1, U18.7
unnamed: C903.1, R901.1, U19.7
unnamed: C1003.1, R1001.1, U20.8
STIM_CHB_SHARED: J5.49, J6.50, MC2.66, R32.1
STIM_CHIP1_SPI_DL: J6.60, MC1.41
STIM_CHIP1_SPI_DR: J6.58, MC1.40
STIM_CHIP2_SPI_DL: J6.26, MC1.39
STIM_CHIP2_SPI_DR: J6.24, MC1.38
STIM_CHIP3_SPI_DL: J5.59, MC2.58
STIM_CHIP3_SPI_DR: J5.57, MC2.57
STIM_CHIP4_SPI_DL: J5.25, MC2.56
STIM_CHIP4_SPI_DR: J5.23, MC2.31
STIM_CLK_SHARED: J5.53, J6.54, MC2.69, R33.1
STIM_EN_SHARED: J5.51, J6.52, MC2.67, R30.1
STIM_START_SHARED: J5.55, J6.56, MC2.70, R31.1
USBJTAG_5V_IN: C20.2, FB1.1, J4.A4, J4.A9, J4.B4, J4.B9, R15.1, TP5.1
USB_D_N: J4.A7, J4.B7, U3.6
USB_D_P: J4.A6, J4.B6, U3.7
XEM PG: MC1.90, R5.1, U2.4, U21.2
